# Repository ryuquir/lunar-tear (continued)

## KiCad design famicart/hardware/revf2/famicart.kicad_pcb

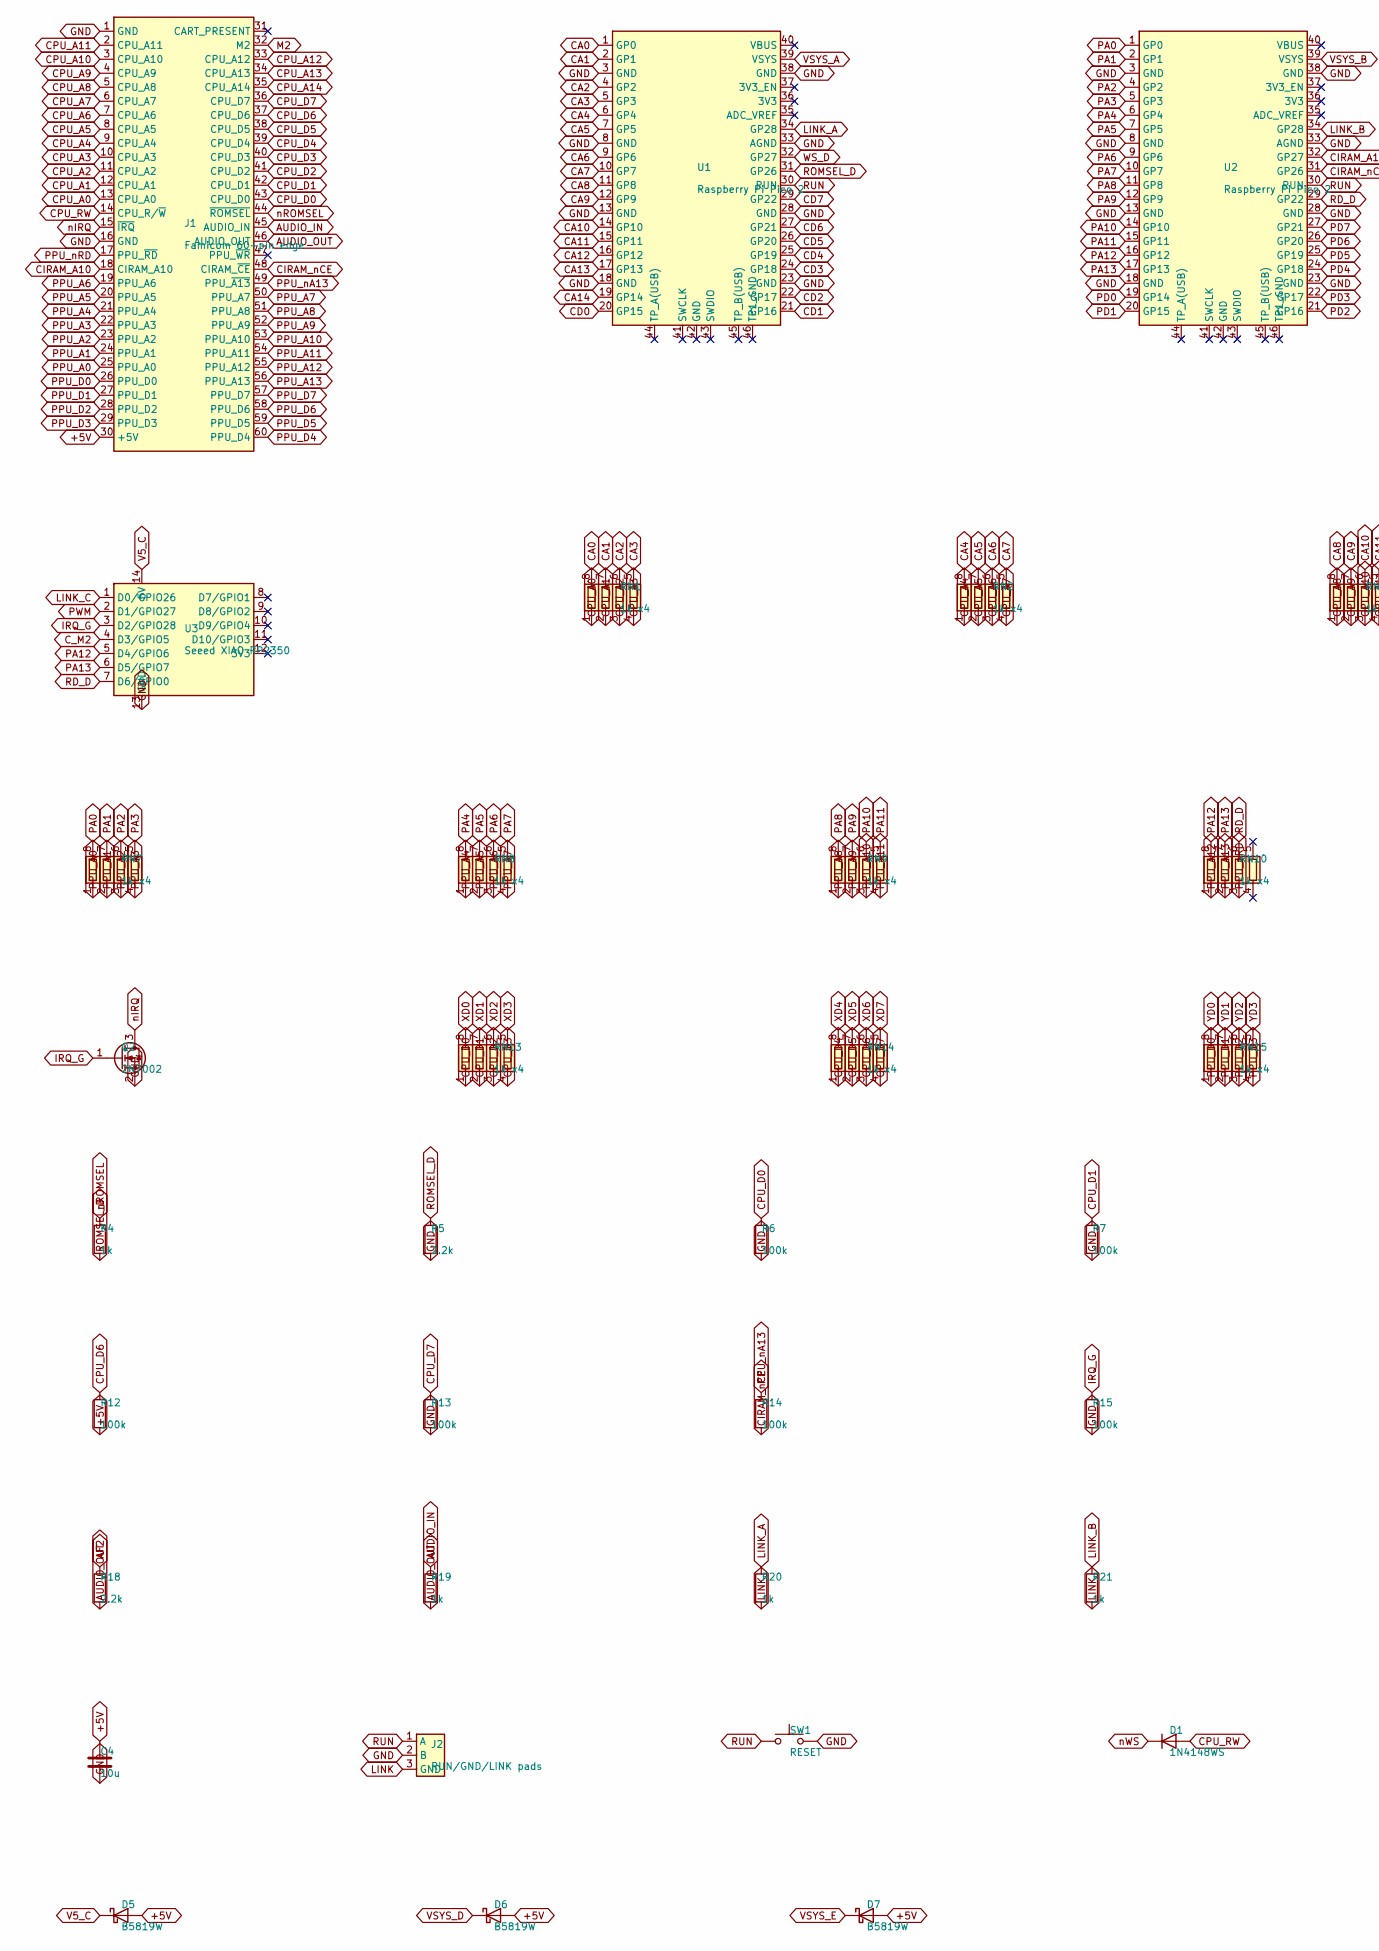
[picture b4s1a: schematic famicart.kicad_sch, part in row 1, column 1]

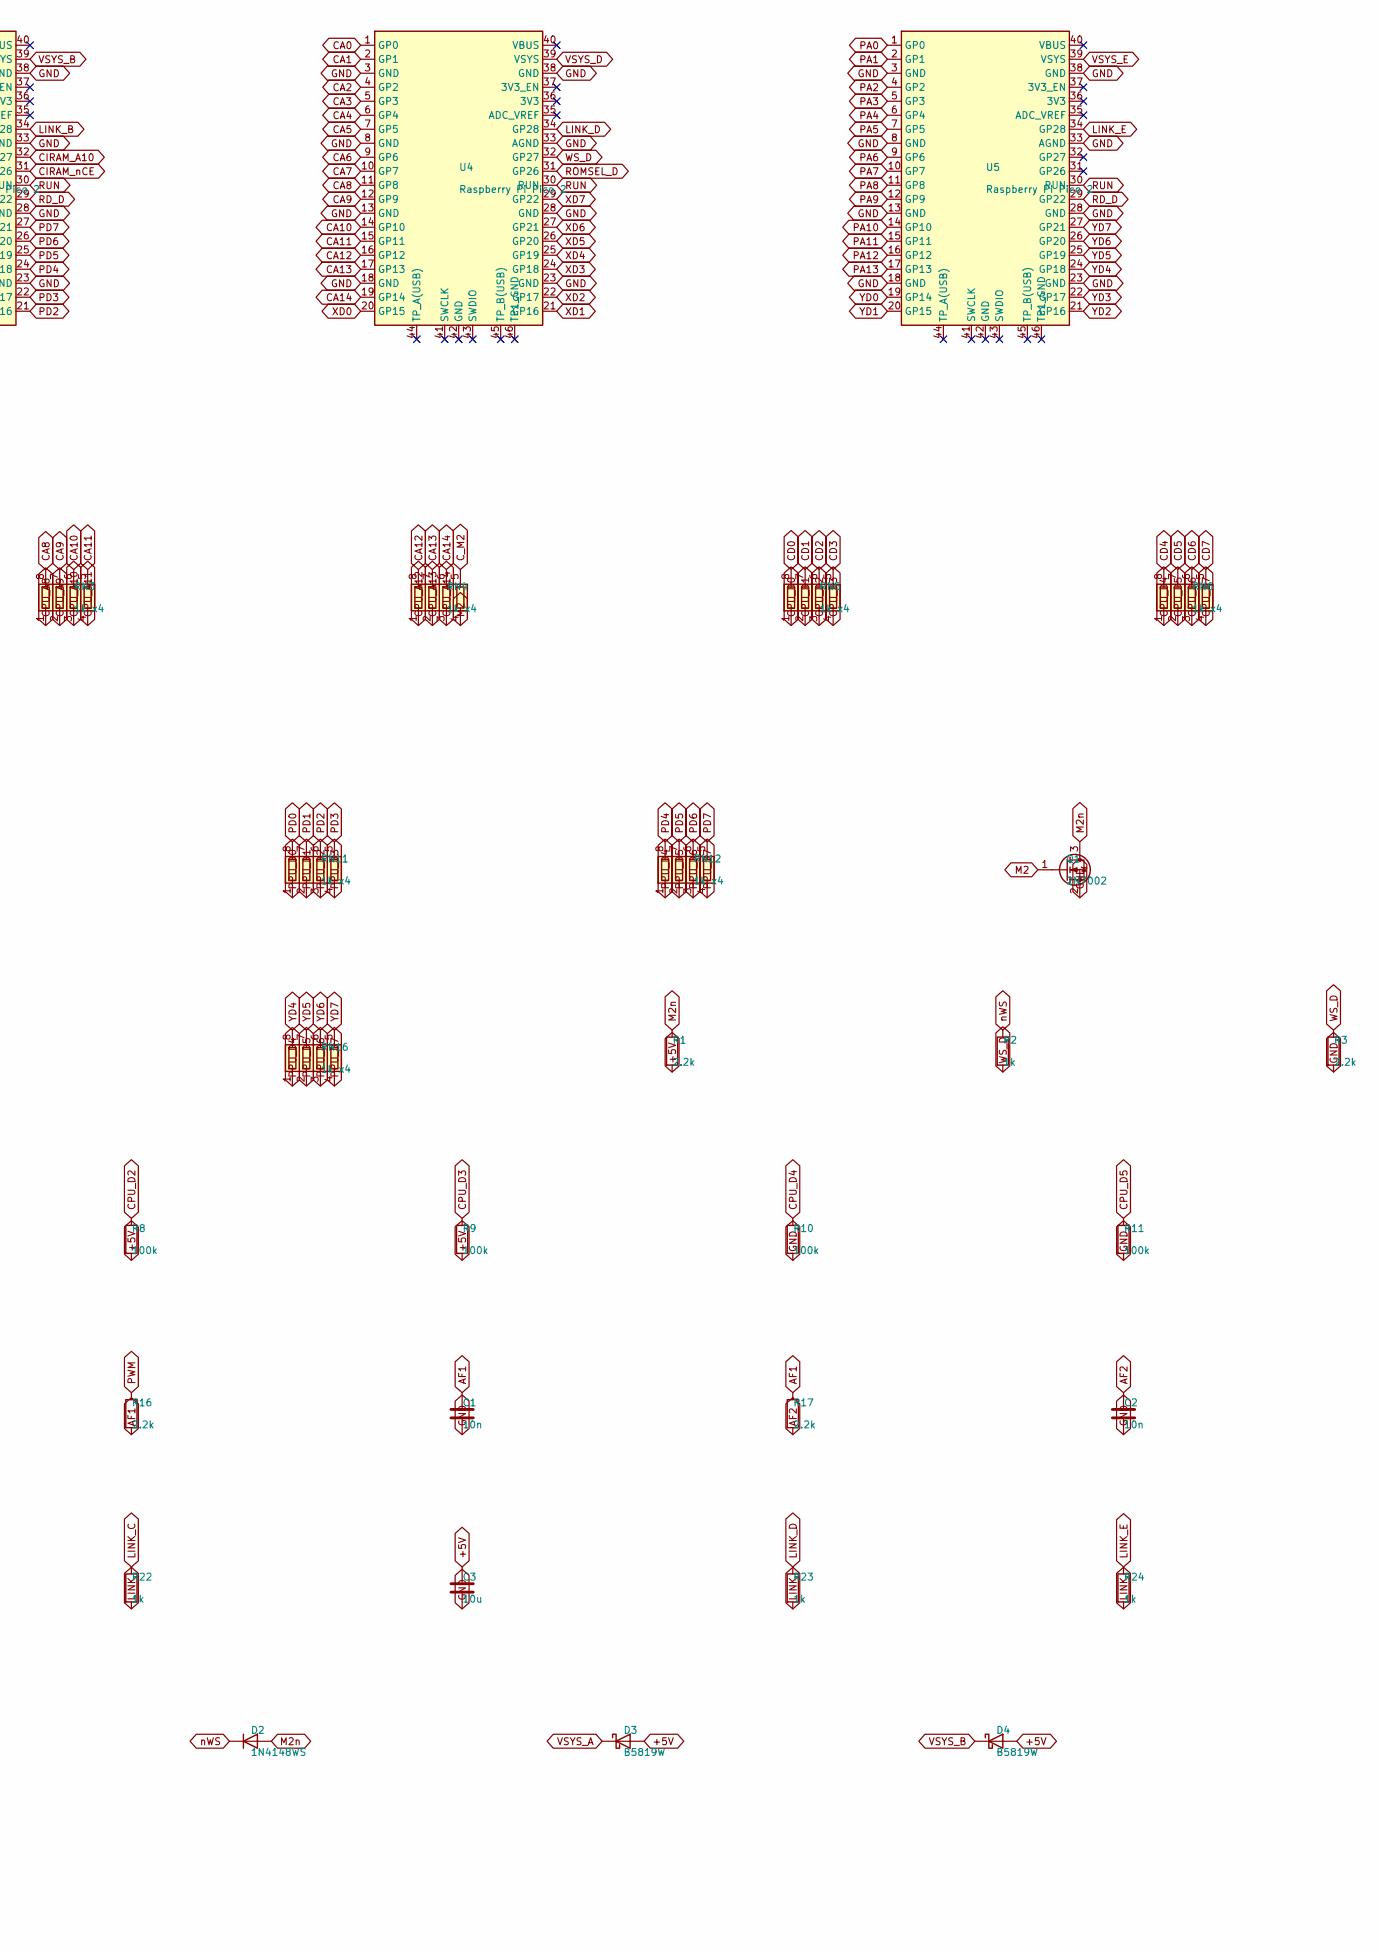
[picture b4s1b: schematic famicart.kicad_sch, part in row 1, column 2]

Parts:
C1, C2: 10n; C_0603_1608Metric
C3, C4: 10u; C_0805_2012Metric
D1, D2: 1N4148WS; D_SOD-323
D3, D4, D5, D6, D7: B5819W; D_SOD-123
J1: Famicom 60-pin edge; Famicom_CardEdge_60
J2: RUN/GND/LINK pads; WirePads_1x3
Q1, Q2: 2N7002; SOT-23
R1, R3, R5, R16, R17, R18: 2.2k; R_0603_1608Metric
R2, R4, R19, R20, R21, R22, R23, R24: 1k; R_0603_1608Metric
R6, R7, R8, R9, R10, R11, R12, R13, R14, R15: 100k; R_0603_1608Metric
RN1, RN2, RN3, RN4, RN5, RN6, RN7, RN8, RN9, RN10, RN11, RN12, RN13, RN14, RN15, RN16: 1k x4; R_Array_Convex_4x0603
SW1: RESET; SW_Push_1P1T_XKB_TS-1187A
U1, U2, U4, U5: Raspberry Pi Pico 2; RPi_Pico_SMD_Short
U3: Seeed XIAO RP2350; XIAO-RP2350-Edge

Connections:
+5V: C3.1, C4.1, D3.2 (A), D4.2 (A), D5.2 (A), D6.2 (A), D7.2 (A), J1.30 (+5V), R1.2, R8.2, R9.2, R12.2
AF1: C1.1, R16.2, R17.1
AF2: C2.1, R17.2, R18.1
AUDIO_IN: J1.45 (AUDIO_IN), R19.1
AUDIO_OUT: J1.46 (AUDIO_OUT), R18.2, R19.2
CA0: RN1.8 (R1.2), U1.1 (GP0), U4.1 (GP0)
CA1: RN1.7 (R2.2), U1.2 (GP1), U4.2 (GP1)
CA2: RN1.6 (R3.2), U1.4 (GP2), U4.4 (GP2)
CA3: RN1.5 (R4.2), U1.5 (GP3), U4.5 (GP3)
CA4: RN2.8 (R1.2), U1.6 (GP4), U4.6 (GP4)
CA5: RN2.7 (R2.2), U1.7 (GP5), U4.7 (GP5)
CA6: RN2.6 (R3.2), U1.9 (GP6), U4.9 (GP6)
CA7: RN2.5 (R4.2), U1.10 (GP7), U4.10 (GP7)
CA8: RN3.8 (R1.2), U1.11 (GP8), U4.11 (GP8)
CA9: RN3.7 (R2.2), U1.12 (GP9), U4.12 (GP9)
CA10: RN3.6 (R3.2), U1.14 (GP10), U4.14 (GP10)
CA11: RN3.5 (R4.2), U1.15 (GP11), U4.15 (GP11)
CA12: RN4.8 (R1.2), U1.16 (GP12), U4.16 (GP12)
CA13: RN4.7 (R2.2), U1.17 (GP13), U4.17 (GP13)
CA14: RN4.6 (R3.2), U1.19 (GP14), U4.19 (GP14)
CD0: RN5.8 (R1.2), U1.20 (GP15)
CD1: RN5.7 (R2.2), U1.21 (GP16)
CD2: RN5.6 (R3.2), U1.22 (GP17)
CD3: RN5.5 (R4.2), U1.24 (GP18)
CD4: RN6.8 (R1.2), U1.25 (GP19)
CD5: RN6.7 (R2.2), U1.26 (GP20)
CD6: RN6.6 (R3.2), U1.27 (GP21)
CD7: RN6.5 (R4.2), U1.29 (GP22)
CIRAM_A10: J1.18 (CIRAM_A10), U2.32 (GP27)
CIRAM_nCE: J1.48 (CIRAM_~CE), R14.2, U2.31 (GP26)
CPU_A0: J1.13 (CPU_A0), RN1.1 (R1.1)
CPU_A1: J1.12 (CPU_A1), RN1.2 (R2.1)
CPU_A2: J1.11 (CPU_A2), RN1.3 (R3.1)
CPU_A3: J1.10 (CPU_A3), RN1.4 (R4.1)
CPU_A4: J1.9 (CPU_A4), RN2.1 (R1.1)
CPU_A5: J1.8 (CPU_A5), RN2.2 (R2.1)
CPU_A6: J1.7 (CPU_A6), RN2.3 (R3.1)
CPU_A7: J1.6 (CPU_A7), RN2.4 (R4.1)
CPU_A8: J1.5 (CPU_A8), RN3.1 (R1.1)
CPU_A9: J1.4 (CPU_A9), RN3.2 (R2.1)
CPU_A10: J1.3 (CPU_A10), RN3.3 (R3.1)
CPU_A11: J1.2 (CPU_A11), RN3.4 (R4.1)
CPU_A12: J1.33 (CPU_A12), RN4.1 (R1.1)
CPU_A13: J1.34 (CPU_A13), RN4.2 (R2.1)
CPU_A14: J1.35 (CPU_A14), RN4.3 (R3.1)
CPU_D0: J1.43 (CPU_D0), R6.1, RN5.1 (R1.1), RN13.1 (R1.1)
CPU_D1: J1.42 (CPU_D1), R7.1, RN5.2 (R2.1), RN13.2 (R2.1)
CPU_D2: J1.41 (CPU_D2), R8.1, RN5.3 (R3.1), RN13.3 (R3.1)
CPU_D3: J1.40 (CPU_D3), R9.1, RN5.4 (R4.1), RN13.4 (R4.1)
CPU_D4: J1.39 (CPU_D4), R10.1, RN6.1 (R1.1), RN14.1 (R1.1)
CPU_D5: J1.38 (CPU_D5), R11.1, RN6.2 (R2.1), RN14.2 (R2.1)
CPU_D6: J1.37 (CPU_D6), R12.1, RN6.3 (R3.1), RN14.3 (R3.1)
CPU_D7: J1.36 (CPU_D7), R13.1, RN6.4 (R4.1), RN14.4 (R4.1)
CPU_RW: D1.2 (A), J1.14 (CPU_R/~W)
C_M2: RN4.5 (R4.2), U3.4 (D3/GPIO5)
GND: C1.2, C2.2, C3.2, C4.2, J1.1 (GND), J1.16 (GND), J2.2 (B), Q1.2 (S), Q2.2 (S), R3.2, R5.2, R6.2, R7.2, R10.2, R11.2, R13.2, R15.2, SW1.2, U1.3 (GND), U1.8 (GND), U1.13 (GND), U1.18 (GND), U1.23 (GND), U1.28 (GND), U1.33 (AGND), U1.38 (GND), U2.3 (GND), U2.8 (GND), U2.13 (GND), U2.18 (GND), U2.23 (GND), U2.28 (GND), U2.33 (AGND), U2.38 (GND), U3.13 (GND), U4.3 (GND), U4.8 (GND), U4.13 (GND), U4.18 (GND), U4.23 (GND), U4.28 (GND), U4.33 (AGND), U4.38 (GND), U5.3 (GND), U5.8 (GND), U5.13 (GND), U5.18 (GND), U5.23 (GND), U5.28 (GND), U5.33 (AGND), U5.38 (GND)
IRQ_G: Q2.1 (G), R15.1, U3.3 (D2/GPIO28)
LINK: J2.3 (GND), R20.2, R21.2, R22.2, R23.2, R24.2
LINK_A: R20.1, U1.34 (GP28)
LINK_B: R21.1, U2.34 (GP28)
LINK_C: R22.1, U3.1 (D0/GPIO26)
LINK_D: R23.1, U4.34 (GP28)
LINK_E: R24.1, U5.34 (GP28)
M2: J1.32 (M2), Q1.1 (G), RN4.4 (R4.1)
M2n: D2.2 (A), Q1.3 (D), R1.1
PA0: RN7.8 (R1.2), U2.1 (GP0), U5.1 (GP0)
PA1: RN7.7 (R2.2), U2.2 (GP1), U5.2 (GP1)
PA2: RN7.6 (R3.2), U2.4 (GP2), U5.4 (GP2)
PA3: RN7.5 (R4.2), U2.5 (GP3), U5.5 (GP3)
PA4: RN8.8 (R1.2), U2.6 (GP4), U5.6 (GP4)
PA5: RN8.7 (R2.2), U2.7 (GP5), U5.7 (GP5)
PA6: RN8.6 (R3.2), U2.9 (GP6), U5.9 (GP6)
PA7: RN8.5 (R4.2), U2.10 (GP7), U5.10 (GP7)
PA8: RN9.8 (R1.2), U2.11 (GP8), U5.11 (GP8)
PA9: RN9.7 (R2.2), U2.12 (GP9), U5.12 (GP9)
PA10: RN9.6 (R3.2), U2.14 (GP10), U5.14 (GP10)
PA11: RN9.5 (R4.2), U2.15 (GP11), U5.15 (GP11)
PA12: RN10.8 (R1.2), U2.16 (GP12), U3.5 (D4/GPIO6), U5.16 (GP12)
PA13: RN10.7 (R2.2), U2.17 (GP13), U3.6 (D5/GPIO7), U5.17 (GP13)
PD0: RN11.8 (R1.2), U2.19 (GP14)
PD1: RN11.7 (R2.2), U2.20 (GP15)
PD2: RN11.6 (R3.2), U2.21 (GP16)
PD3: RN11.5 (R4.2), U2.22 (GP17)
PD4: RN12.8 (R1.2), U2.24 (GP18)
PD5: RN12.7 (R2.2), U2.25 (GP19)
PD6: RN12.6 (R3.2), U2.26 (GP20)
PD7: RN12.5 (R4.2), U2.27 (GP21)
PPU_A0: J1.25 (PPU_A0), RN7.1 (R1.1)
PPU_A1: J1.24 (PPU_A1), RN7.2 (R2.1)
PPU_A2: J1.23 (PPU_A2), RN7.3 (R3.1)
PPU_A3: J1.22 (PPU_A3), RN7.4 (R4.1)
PPU_A4: J1.21 (PPU_A4), RN8.1 (R1.1)
PPU_A5: J1.20 (PPU_A5), RN8.2 (R2.1)
PPU_A6: J1.19 (PPU_A6), RN8.3 (R3.1)
PPU_A7: J1.50 (PPU_A7), RN8.4 (R4.1)
PPU_A8: J1.51 (PPU_A8), RN9.1 (R1.1)
PPU_A9: J1.52 (PPU_A9), RN9.2 (R2.1)
PPU_A10: J1.53 (PPU_A10), RN9.3 (R3.1)
PPU_A11: J1.54 (PPU_A11), RN9.4 (R4.1)
PPU_A12: J1.55 (PPU_A12), RN10.1 (R1.1)
PPU_A13: J1.56 (PPU_A13), RN10.2 (R2.1)
PPU_D0: J1.26 (PPU_D0), RN11.1 (R1.1), RN15.1 (R1.1)
PPU_D1: J1.27 (PPU_D1), RN11.2 (R2.1), RN15.2 (R2.1)
PPU_D2: J1.28 (PPU_D2), RN11.3 (R3.1), RN15.3 (R3.1)
PPU_D3: J1.29 (PPU_D3), RN11.4 (R4.1), RN15.4 (R4.1)
PPU_D4: J1.60 (PPU_D4), RN12.1 (R1.1), RN16.1 (R1.1)
PPU_D5: J1.59 (PPU_D5), RN12.2 (R2.1), RN16.2 (R2.1)
PPU_D6: J1.58 (PPU_D6), RN12.3 (R3.1), RN16.3 (R3.1)
PPU_D7: J1.57 (PPU_D7), RN12.4 (R4.1), RN16.4 (R4.1)
PPU_nA13: J1.49 (PPU_~A13), R14.1
PPU_nRD: J1.17 (PPU_~RD), RN10.3 (R3.1)
PWM: R16.1, U3.2 (D1/GPIO27)
RD_D: RN10.6 (R3.2), U2.29 (GP22), U3.7 (D6/GPIO0), U5.29 (GP22)
ROMSEL_D: R4.2, R5.1, U1.31 (GP26), U4.31 (GP26)
RUN: J2.1 (A), SW1.1, U1.30 (RUN), U2.30 (RUN), U4.30 (RUN), U5.30 (RUN)
V5_C: D5.1 (K), U3.14 (5V)
VSYS_A: D3.1 (K), U1.39 (VSYS)
VSYS_B: D4.1 (K), U2.39 (VSYS)
VSYS_D: D6.1 (K), U4.39 (VSYS)
VSYS_E: D7.1 (K), U5.39 (VSYS)
WS_D: R2.2, R3.1, U1.32 (GP27), U4.32 (GP27)
XD0: RN13.8 (R1.2), U4.20 (GP15)
XD1: RN13.7 (R2.2), U4.21 (GP16)
XD2: RN13.6 (R3.2), U4.22 (GP17)
XD3: RN13.5 (R4.2), U4.24 (GP18)
XD4: RN14.8 (R1.2), U4.25 (GP19)
XD5: RN14.7 (R2.2), U4.26 (GP20)
XD6: RN14.6 (R3.2), U4.27 (GP21)
XD7: RN14.5 (R4.2), U4.29 (GP22)
YD0: RN15.8 (R1.2), U5.19 (GP14)
YD1: RN15.7 (R2.2), U5.20 (GP15)
YD2: RN15.6 (R3.2), U5.21 (GP16)
YD3: RN15.5 (R4.2), U5.22 (GP17)
YD4: RN16.8 (R1.2), U5.24 (GP18)
YD5: RN16.7 (R2.2), U5.25 (GP19)
YD6: RN16.6 (R3.2), U5.26 (GP20)
YD7: RN16.5 (R4.2), U5.27 (GP21)
nIRQ: J1.15 (~IRQ), Q2.3 (D)
nROMSEL: J1.44 (~ROMSEL), R4.1
nWS: D1.1 (K), D2.1 (K), R2.1

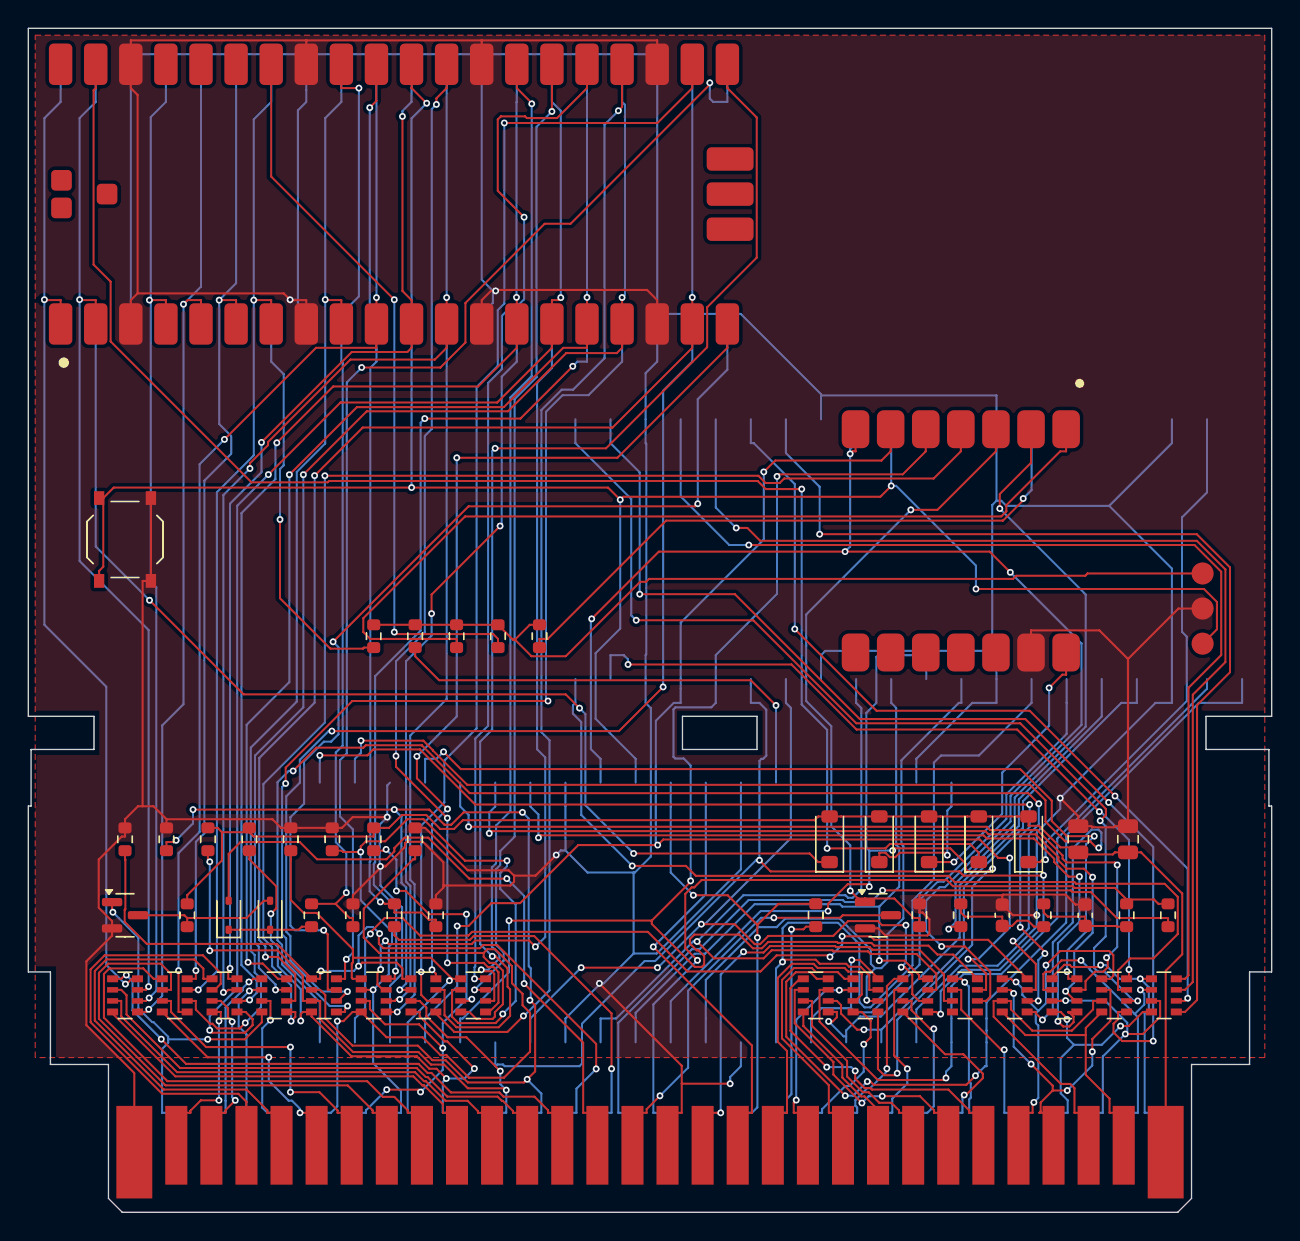
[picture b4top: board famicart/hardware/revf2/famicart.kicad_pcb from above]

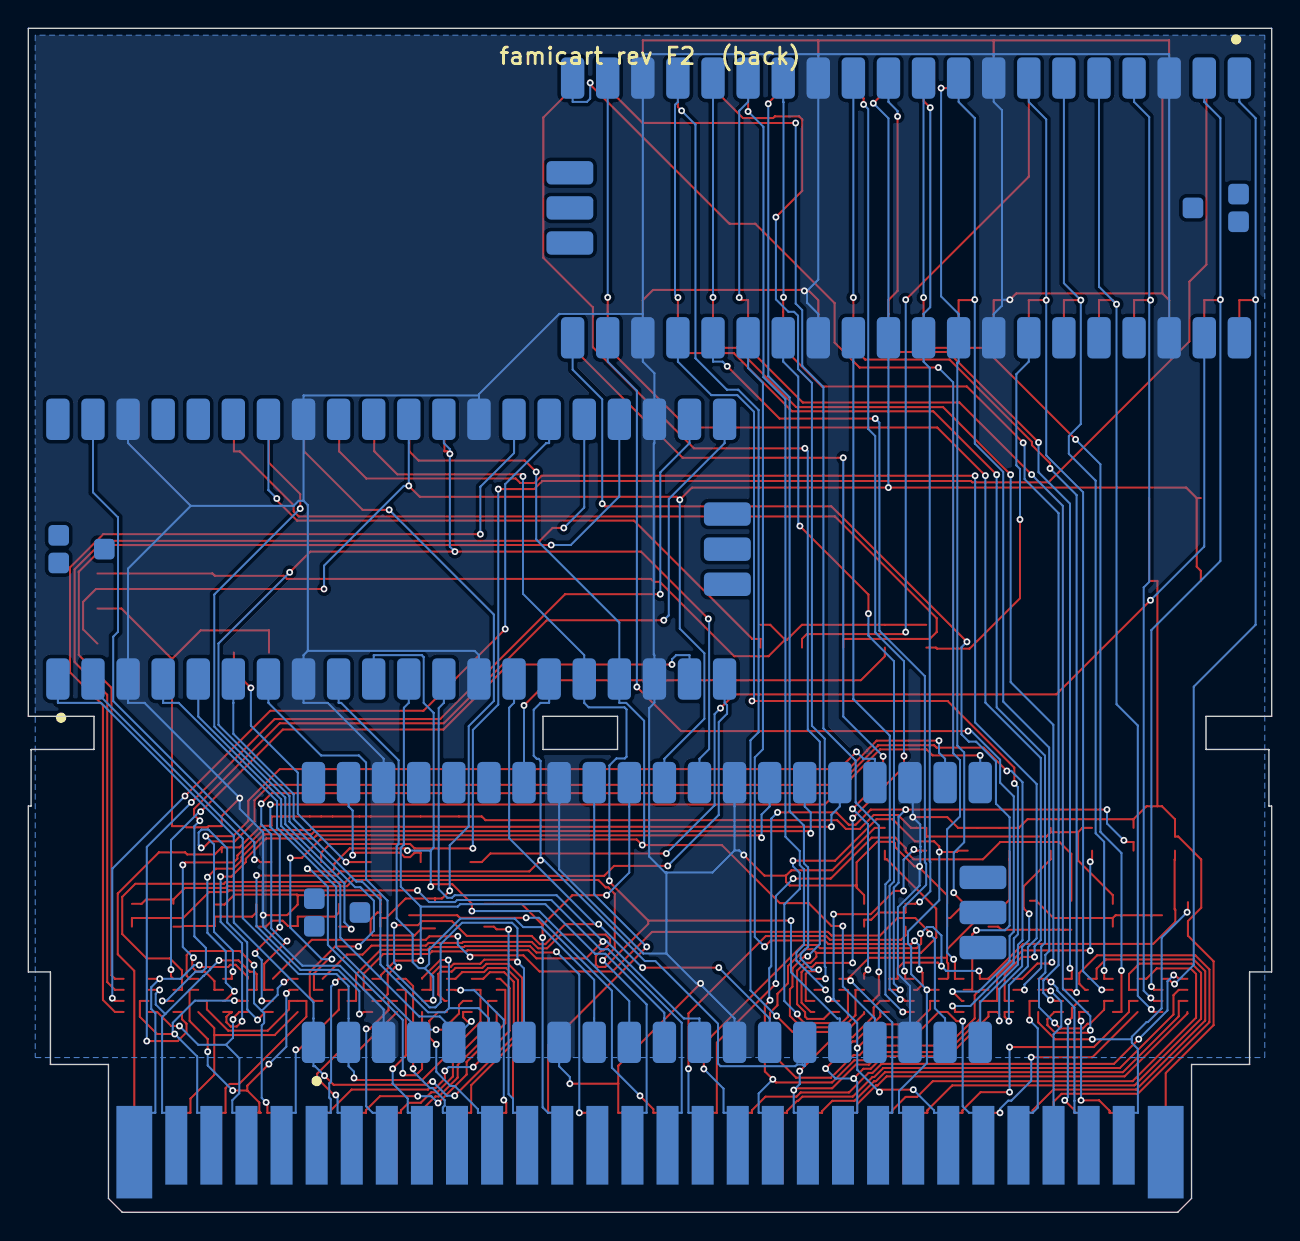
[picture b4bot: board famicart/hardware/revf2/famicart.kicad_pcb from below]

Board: 2 copper layers, 90.0 x 85.7 mm, 61 parts (3 on the bottom side), 140 nets.

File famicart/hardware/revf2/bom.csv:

Qty,Value,Footprint,References,Suggested part
1,Famicom 60-pin edge,Famicom_CardEdge_60,J1,"PCB card edge (gold fingers), no part"
4,Raspberry Pi Pico 2,RPi_Pico_SMD_Short,U1 U2 U4 U5,Raspberry Pi SC1631 (Pico 2) / Pico (RP2040) also fits
1,Seeed XIAO RP2350,XIAO-RP2350-Edge,U3,
16,1k x4,R_Array_Convex_4x0603,RN1 RN2 RN3 RN4 RN5 RN6 RN7 RN8 RN9 RN10 RN11 RN12 RN13 RN14 RN15 RN16,
2,2N7002,SOT-23,Q1 Q2,
6,2.2k,R_0603_1608Metric,R1 R3 R5 R16 R17 R18,0603 1%
2,1N4148WS,D_SOD-323,D1 D2,
8,1k,R_0603_1608Metric,R2 R4 R19 R20 R21 R22 R23 R24,0603 1%
10,100k,R_0603_1608Metric,R6 R7 R8 R9 R10 R11 R12 R13 R14 R15,
2,10n,C_0603_1608Metric,C1 C2,X7R 0603 50V
5,B5819W,D_SOD-123,D3 D4 D5 D6 D7,
2,10u,C_0805_2012Metric,C3 C4,X5R 0805 10V
1,RESET,SW_Push_1P1T_XKB_TS-1187A,SW1,E-Switch TL3342 / any 4.7x3.5 mm low-profile tactile
1,RUN/GND/LINK pads,WirePads_1x3,J2,
